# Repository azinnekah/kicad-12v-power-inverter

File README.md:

*PCB Project 1: 12V Power Inverter - Adam Zinnekah 5/20/26*
*Inspired by @diyhideout on their mini inverter.*
*Circuit topology based on standard reference application schematics for the IR2153 Half-Bridge gate driver.*
**Circuit has passed DRC gates in KiCad but has not been manufactured nor tested. Preparing the Gerber files for potential fabrication in the future.**

*This layout PCB is an introduction to the KiCad EDA workflow, from schematic capture, objection creation and implementation, PCB design and 3D modelling, and route-tracing.*

**Tweaks I have made to the design and why**

**Widended Power Delivery Top Rails**
*Expanded the 0.4mm trace width to 1.5mm to prevent potential parasitic voltage drops and preventing board delamination.*

**Replaced potentiometer from acptechnologies CA6 unit that was recommended to Bourns 3296W Vertical 3-pin**
*Bourns pot had 3d project files built-in to KiCad workspace, and provides more precision tuning for resistance values to control the RC time constant.*

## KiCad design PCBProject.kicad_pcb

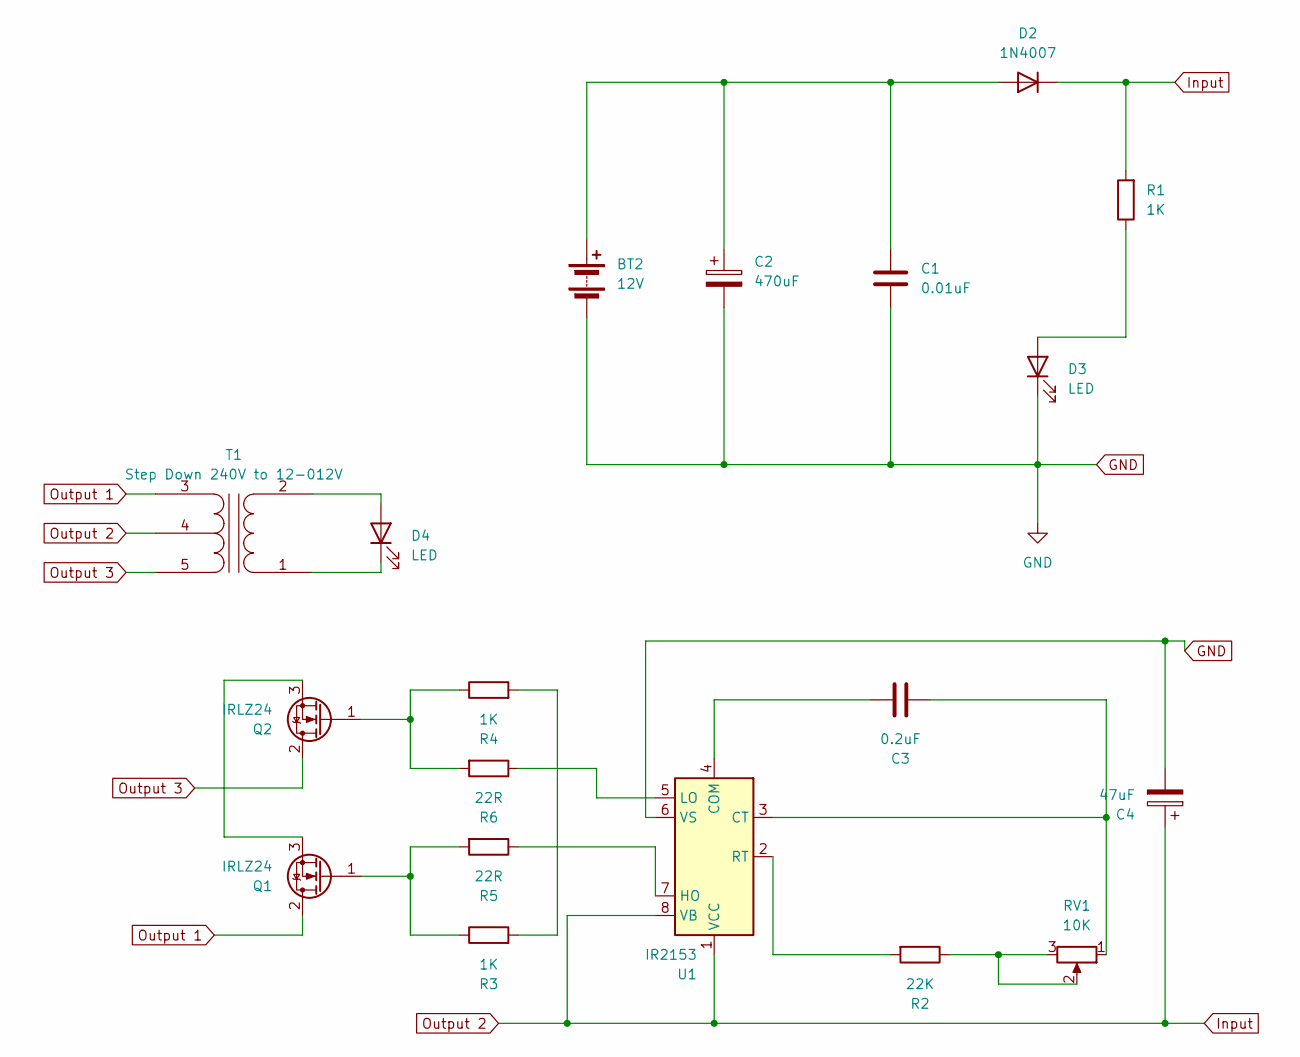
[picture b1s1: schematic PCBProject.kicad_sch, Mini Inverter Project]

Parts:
BT2: 12V; TerminalBlock_Xinya_XY308-2.54-2P_1x02_P2.54mm_Horizontal
C1: 0.01uF; C_Disc_D3.0mm_W1.6mm_P2.50mm
C2: 470uF; CP_Radial_D6.3mm_P2.50mm
C3: 0.2uF; C_Disc_D3.0mm_W1.6mm_P2.50mm
C4: 47uF; CP_Radial_D5.0mm_P2.50mm
D2: 1N4007; D_DO-41_SOD81_P10.16mm_Horizontal
D3: LED; LED_D5.0mm
D4: LED; TerminalBlock_Xinya_XY308-2.54-2P_1x02_P2.54mm_Horizontal
Q1, Q2: IRLZ24; TO-220-3_Vertical
R1, R3, R4: 1K; R_Axial_DIN0204_L3.6mm_D1.6mm_P5.08mm_Horizontal
R2: 22K; R_Axial_DIN0204_L3.6mm_D1.6mm_P5.08mm_Horizontal
R5, R6: 22R; R_Axial_DIN0204_L3.6mm_D1.6mm_P5.08mm_Horizontal
RV1: 10K; Potentiometer_Bourns_3296W_Vertical
T1: Step Down 240V to 12-012V; TerminalBlock_Xinya_XY308-2.54-5P_1x05_P2.54mm_Horizontal
U1: IR2153; DIP-8_W7.62mm

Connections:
GND: BT2.2 (-), C1.2, C2.2, C4.2, D3.1 (K), U1.6 (VS)
Input: C4.1, D2.1 (K), R1.2, T1.4 (SC), U1.1 (VCC), U1.8 (VB)
unnamed: BT2.1 (+), C1.1, C2.1, D2.2 (A)
unnamed: D3.2 (A), R1.1
unnamed: D4.2 (A), T1.2 (AB)
unnamed: D4.1 (K), T1.1 (AA)
unnamed: Q1.1 (G), R3.1, R5.2
unnamed: Q1.3 (S), Q2.3 (S)
unnamed: Q2.1 (G), R4.1, R6.2
unnamed: R2.1, RV1.2, RV1.3
unnamed: R3.2, R4.2
unnamed: C3.2, U1.4 (COM)
unnamed: C3.1, RV1.1, U1.3 (CT)
unnamed: R5.1, U1.7 (HO)
unnamed: R6.1, U1.5 (LO)
unnamed: R2.2, U1.2 (RT)
Output 1: Q1.2 (D), T1.3 (SA)
Output 3: Q2.2 (D), T1.5 (SB)

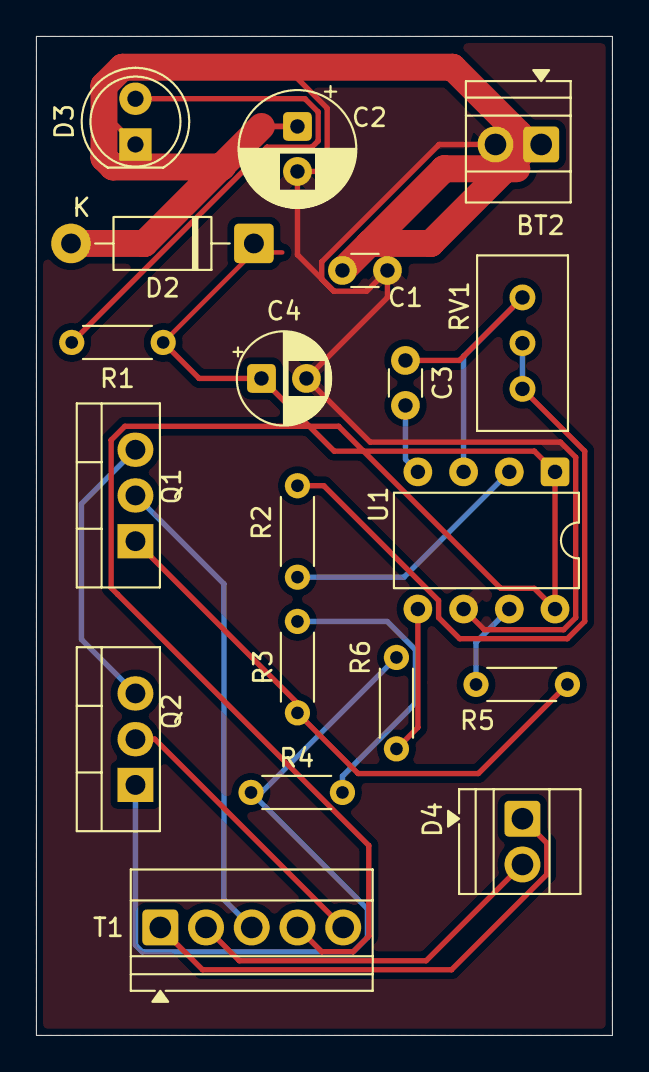
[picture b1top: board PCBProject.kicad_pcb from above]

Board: 2 copper layers, 32.0 x 55.5 mm, 19 parts (0 on the bottom side), 18 nets.

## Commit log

2026-05-23 Initial commit: Completed Intro Mini Inverter KiCad PCB project layout
2026-05-23 Create README.md
    Create README for project, crediting original idea and adding rationale for tweaks to initial design
2026-05-23 Fix: remove temporary lock files, zip archives, and local history
